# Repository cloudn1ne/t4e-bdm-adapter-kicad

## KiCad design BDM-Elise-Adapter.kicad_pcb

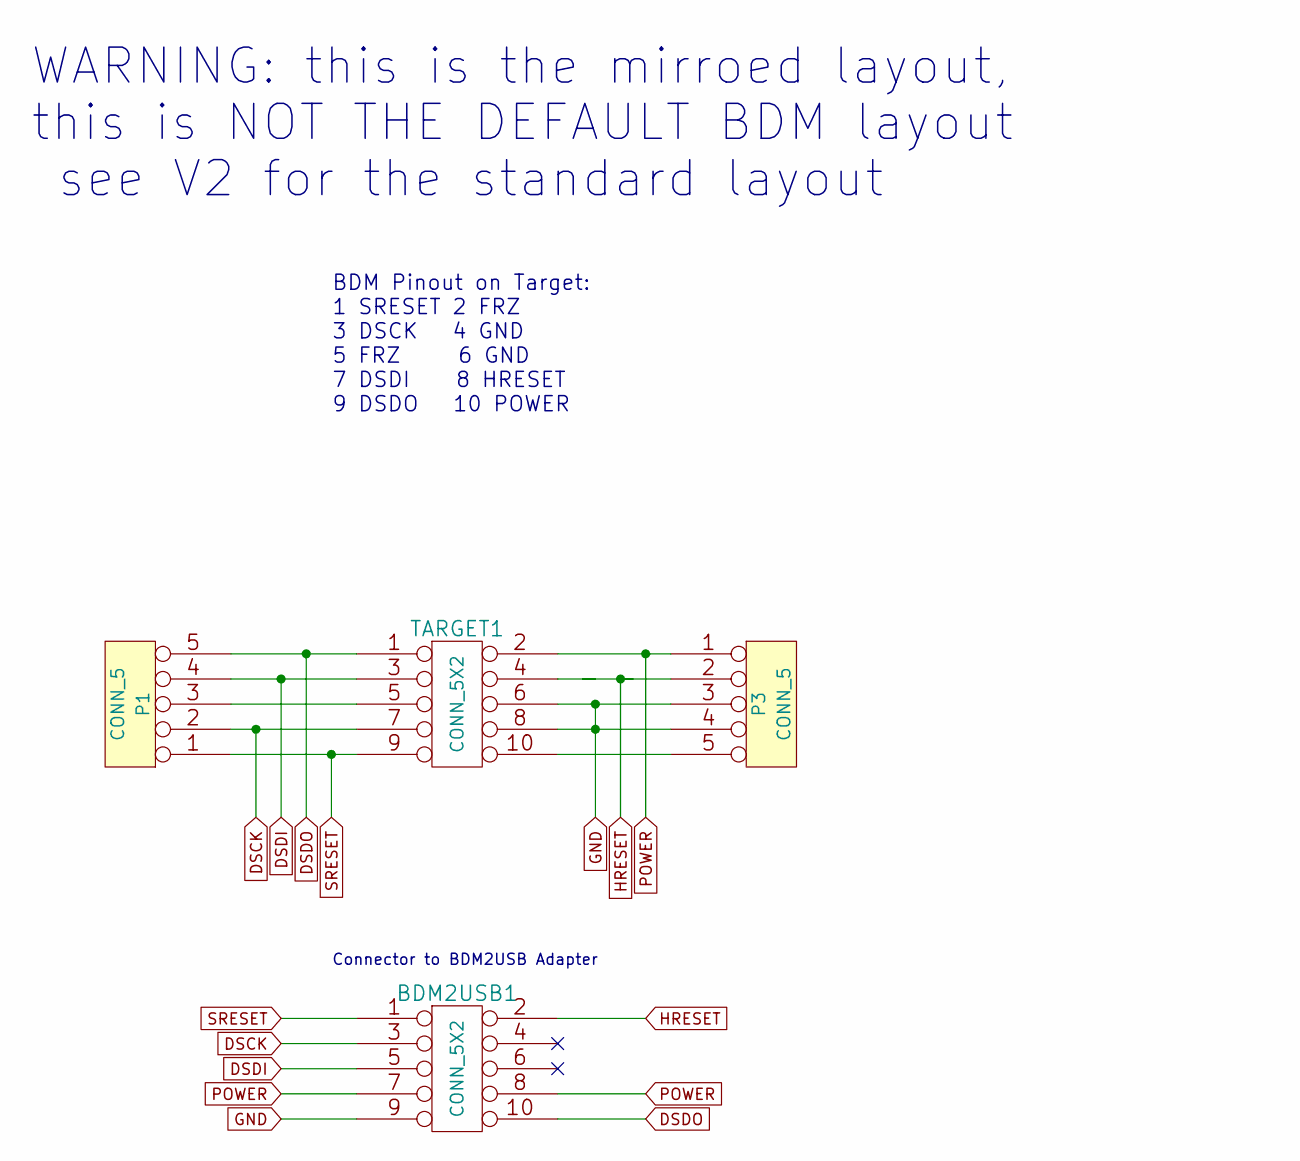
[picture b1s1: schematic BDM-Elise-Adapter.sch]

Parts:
BDM2USB1: CONN_5X2
P1, P3: CONN_5
TARGET1: CONN_5X2

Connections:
DSCK: BDM2USB1.3, P1.2, TARGET1.7
DSDI: BDM2USB1.5, P1.4, TARGET1.3
DSDO: BDM2USB1.10, P1.5, TARGET1.1
GND: BDM2USB1.9, P3.3, P3.4, TARGET1.6, TARGET1.8
HRESET: BDM2USB1.2, P3.2, TARGET1.4
unnamed: P3.5, TARGET1.10
unnamed: P1.3, TARGET1.5
POWER: BDM2USB1.7, BDM2USB1.8, P3.1, TARGET1.2
SRESET: BDM2USB1.1, P1.1, TARGET1.9

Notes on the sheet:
BDM Pinout on Target: 1 SRESET 2 FRZ 3 DSCK 4 GND 5 FRZ 6 GND 7 DSDI 8 HRESET 9 DSDO 10 POWER
Connector to BDM2USB Adapter
WARNING: this is the mirroed layout, this is NOT THE DEFAULT BDM layout see V2 for the standard layout

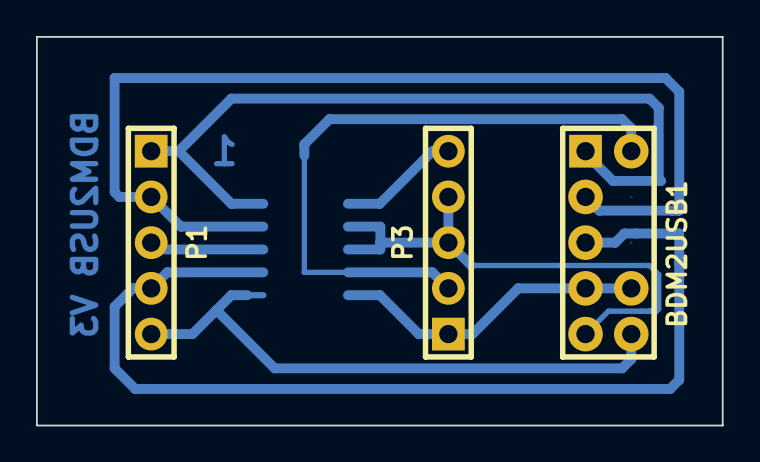
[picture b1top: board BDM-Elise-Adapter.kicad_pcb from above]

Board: 2 copper layers, 38.1 x 21.6 mm, 4 parts (1 on the bottom side), 9 nets.
